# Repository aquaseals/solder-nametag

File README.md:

# solder-nametag
My first PCB! A simple nametag with an  LED that lights up in the dark using a photoresistor, and another LED whose light intensity fades in with a push of a button using a capacitor. I added pictures of the sun and moon to represent their presence in the form of the LED light depending on whether the surroundings are dark (night) or have light (day).

slack username: @haya

## Bill of Materials
- 2 Battery Cells
- 2 Resistors
- 2 LEDs
- 1 Photoresistor
- 1 Capacitor
- 1 Push Button

## Schematic

## PCB Design

## 3D View

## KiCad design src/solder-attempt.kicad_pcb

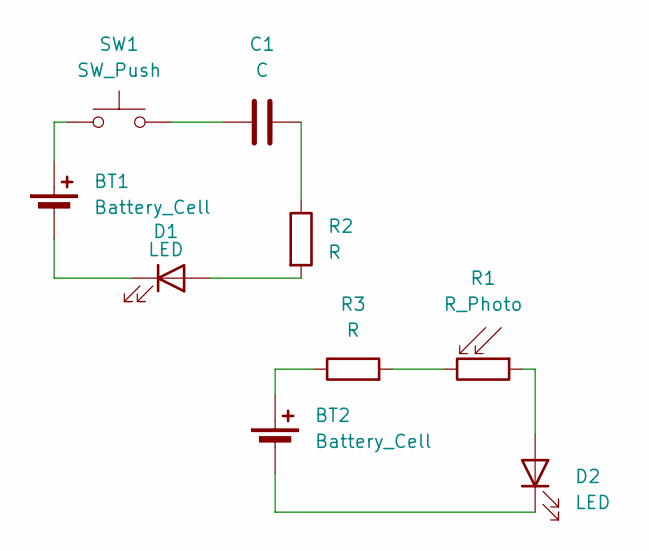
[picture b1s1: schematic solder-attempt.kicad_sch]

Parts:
BT1, BT2: Battery_Cell; BatteryHolder_Keystone_3034_1x20mm
C1: C; CP_Radial_D8.0mm_P5.00mm
D1, D2: LED; LED_D5.0mm
R1: R_Photo; R_LDR_5.1x4.3mm_P3.4mm_Vertical
R2, R3: R; R_Axial_DIN0207_L6.3mm_D2.5mm_P7.62mm_Horizontal
SW1: SW_Push; SW_PUSH_6mm

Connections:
unnamed: BT1.1 (+), SW1.1
unnamed: BT1.2 (-), D1.1 (K)
unnamed: BT2.1 (+), R3.1
unnamed: BT2.2 (-), D2.1 (K)
unnamed: C1.1, SW1.2
unnamed: C1.2, R2.1
unnamed: D1.2 (A), R2.2
unnamed: D2.2 (A), R1.1
unnamed: R1.2, R3.2

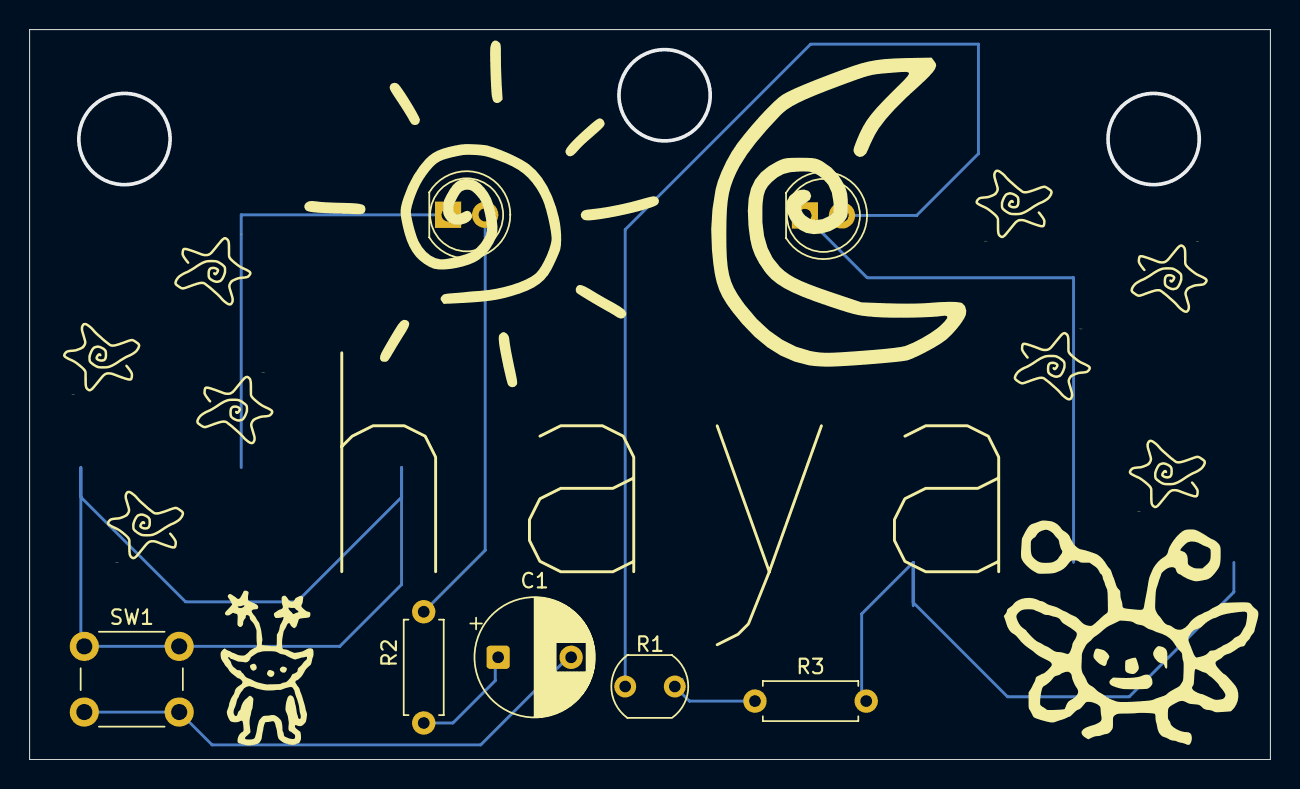
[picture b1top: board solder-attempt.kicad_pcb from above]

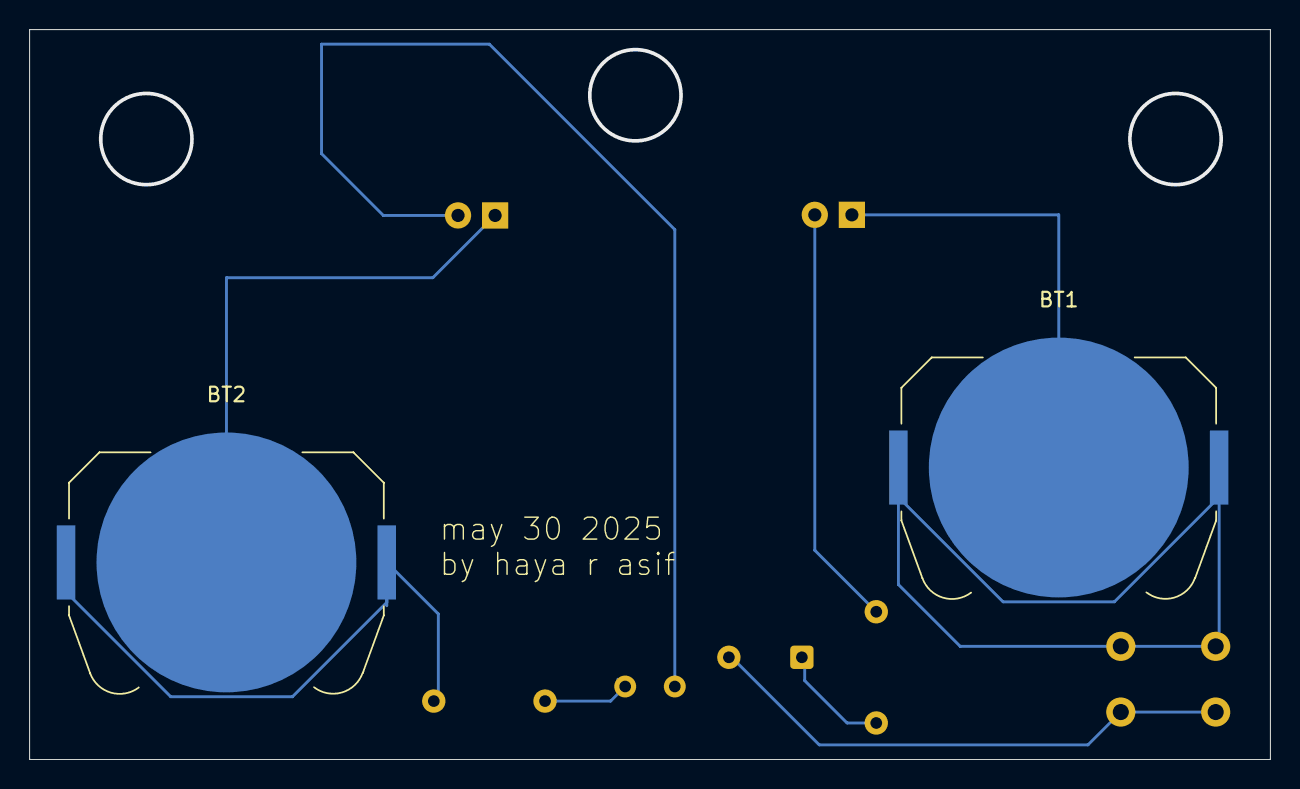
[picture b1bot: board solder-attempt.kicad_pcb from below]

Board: 2 copper layers, 85.0 x 50.0 mm, 9 parts (2 on the bottom side), 9 nets.

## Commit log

2025-05-30 added main files
2025-05-30 organized files
2025-05-30 more organizing
